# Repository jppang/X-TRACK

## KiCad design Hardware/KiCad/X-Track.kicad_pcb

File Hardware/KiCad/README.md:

使用KiCad來重新設計X-TRACK之原理圖及電路圖。

Utilizing KiCad to redesign X-TRACK's schematic and pcb layout.

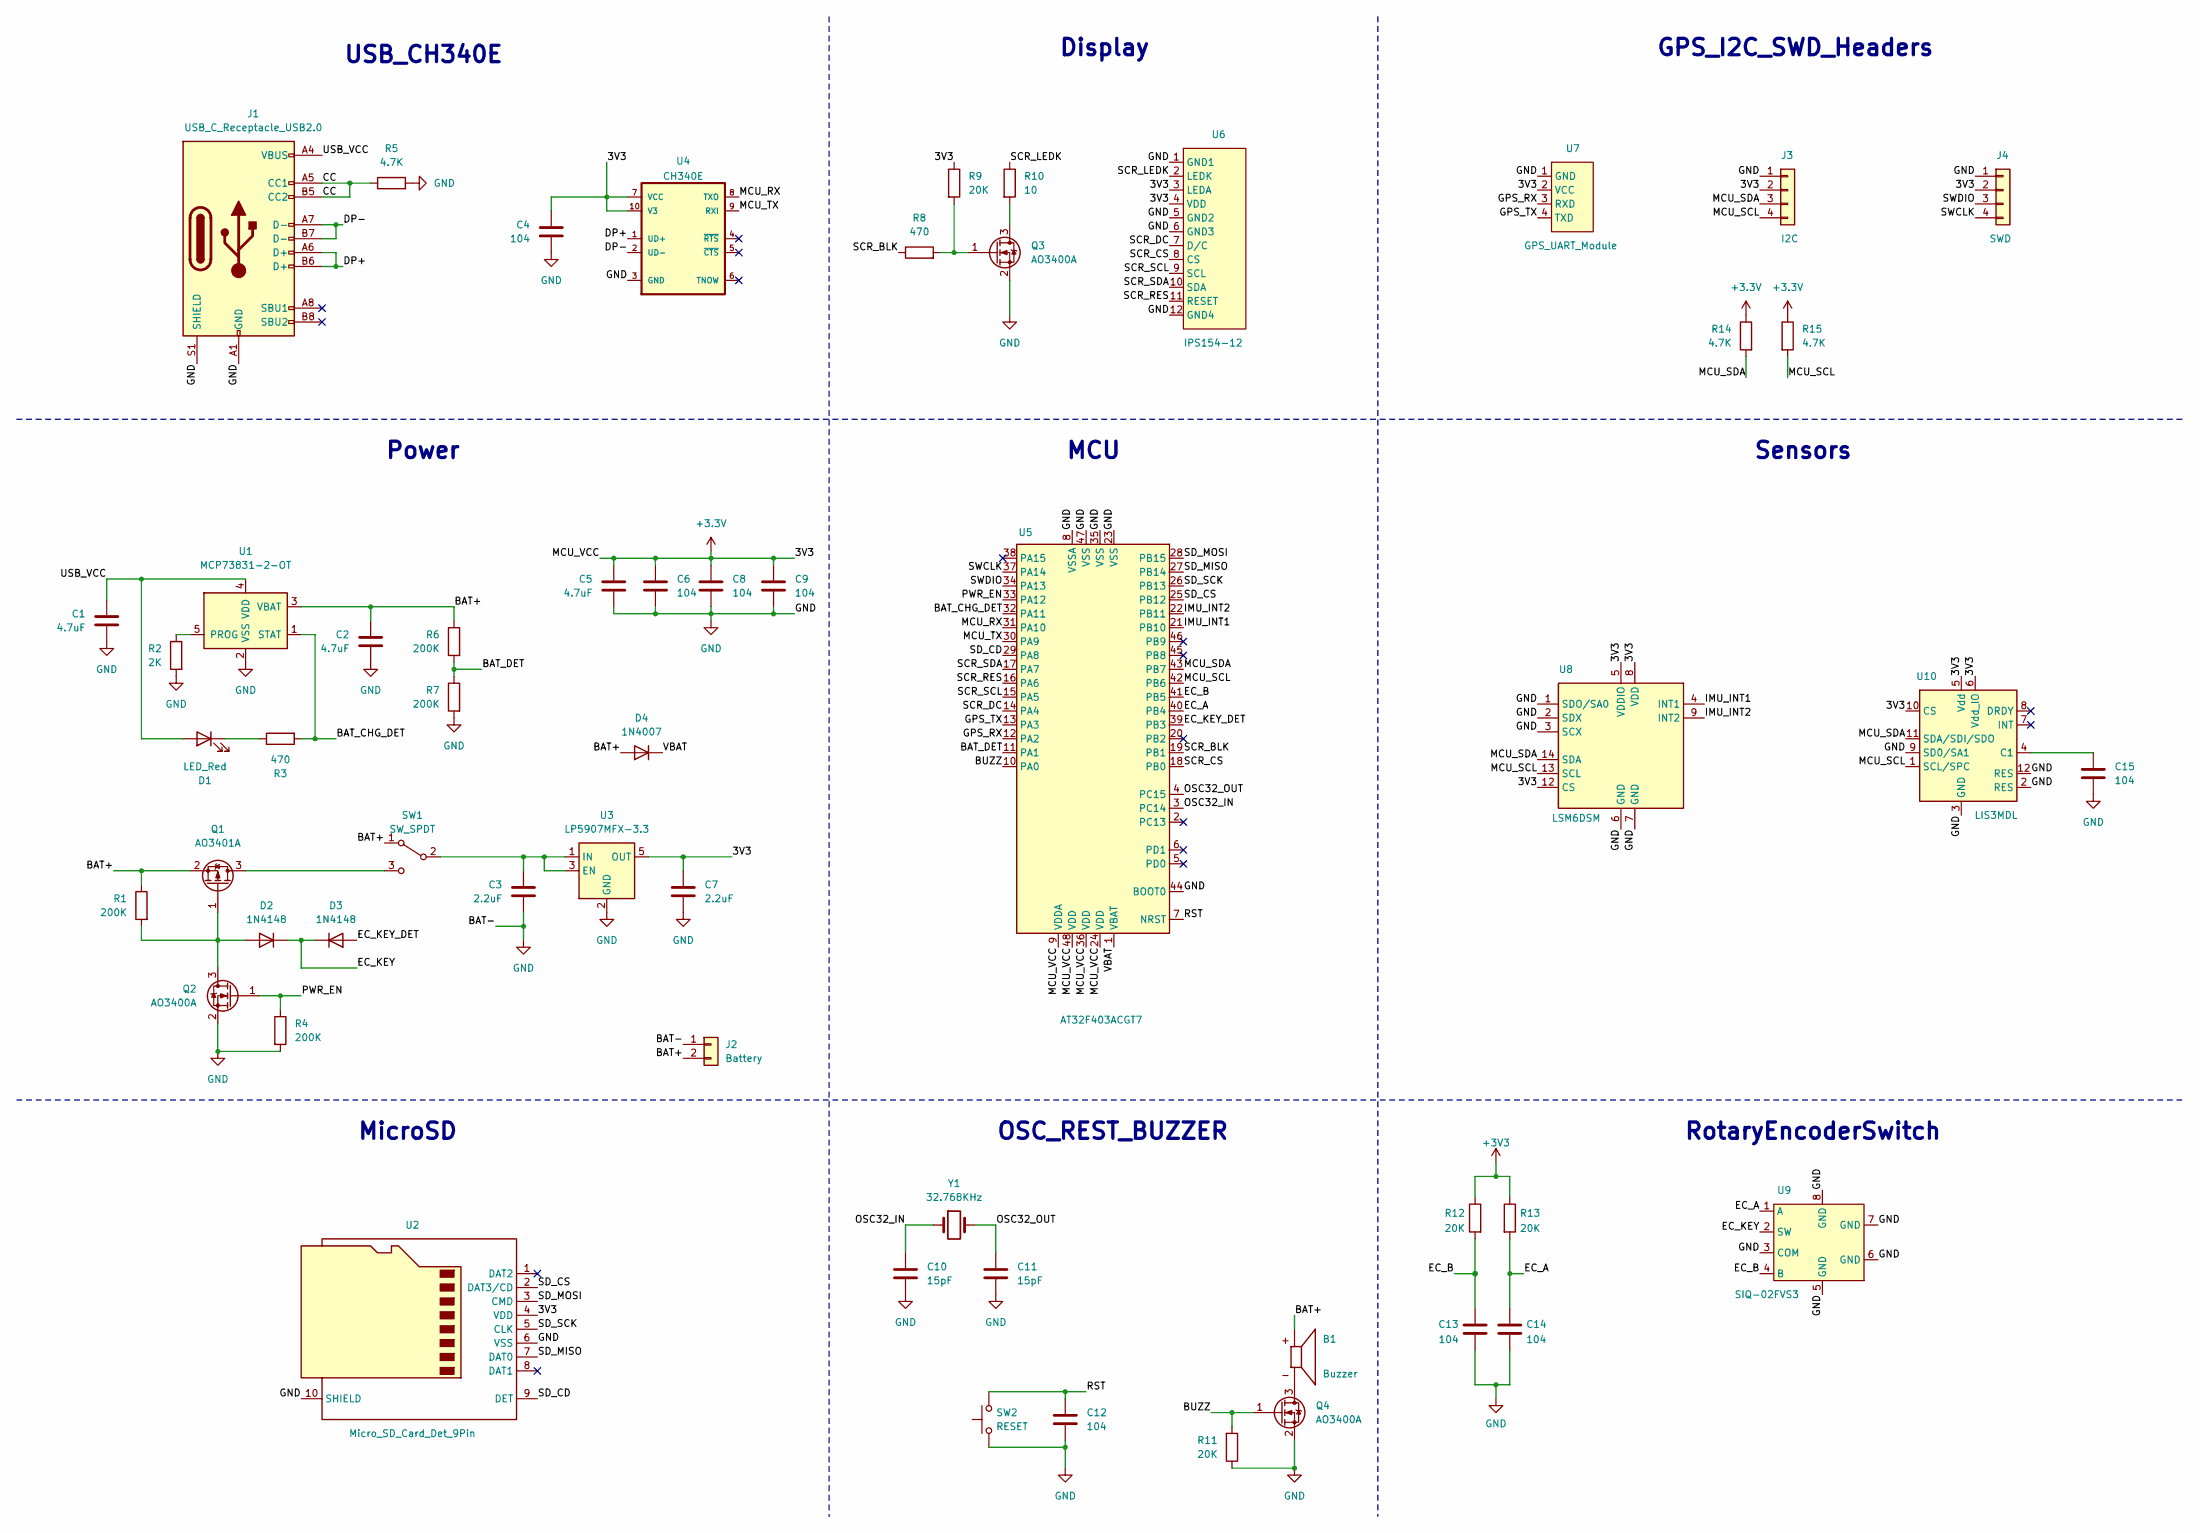
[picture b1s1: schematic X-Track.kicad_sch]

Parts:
B1: Buzzer; Buzzer_CMT-0502-75-SMT-TR; PARTREV 1.0
C1, C2, C5: 4.7uF; C_0805_2012Metric_Pad1.18x1.45mm_HandSolder
C3, C7: 2.2uF; C_0805_2012Metric_Pad1.18x1.45mm_HandSolder
C4, C6, C8, C9, C12, C13, C14, C15: 104; C_0805_2012Metric_Pad1.18x1.45mm_HandSolder
C10, C11: 15pF; C_0805_2012Metric_Pad1.18x1.45mm_HandSolder
D1: LED_Red; LED_0805_2012Metric_Pad1.15x1.40mm_HandSolder
D2, D3: 1N4148; D_0805_2012Metric_Pad1.15x1.40mm_HandSolder
D4: 1N4007; D_0805_2012Metric_Pad1.15x1.40mm_HandSolder
J1: USB_C_Receptacle_USB2.0; Taobao_USB_C_Receptacle_16Pin
J2: Battery; JST_PH_B2B-PH-K_1x02_P2.00mm_Vertical
J3: I2C; JST_PH_B4B-PH-K_1x04_P2.00mm_Vertical
J4: SWD; JST_PH_B4B-PH-K_1x04_P2.00mm_Vertical
Q1: AO3401A; SOT-23
Q2, Q3, Q4: AO3400A; SOT-23
R1, R4, R6, R7: 200K; R_0805_2012Metric_Pad1.20x1.40mm_HandSolder
R2: 2K; R_0805_2012Metric_Pad1.20x1.40mm_HandSolder
R3, R8: 470; R_0805_2012Metric_Pad1.20x1.40mm_HandSolder
R5, R14, R15: 4.7K; R_0805_2012Metric_Pad1.20x1.40mm_HandSolder
R9, R11, R12, R13: 20K; R_0805_2012Metric_Pad1.20x1.40mm_HandSolder
R10: 10; R_0805_2012Metric_Pad1.20x1.40mm_HandSolder
SW1: SW_SPDT; Taobao_SW_SPDT_MSK-12C01-07
SW2: RESET; SW_Push_SPST_NO_Alps_SKRK
U1: MCP73831-2-OT; SOT-23-5
U2: Micro_SD_Card_Det_9Pin; microSD_9Pins
U3: LP5907MFX-3.3; SOT-23-5
U4: CH340E; MSOP-10_3x3mm_P0.5mm
U5: AT32F403ACGT7; LQFP_LQFN_-48_7x7mm_P0.5mm
U6: IPS154-12; ZJY154T-PG04
U7: GPS_UART_Module; JST_PH_B4B-PH-K_1x04_P2.00mm_Vertical
U8: LSM6DSM; LGA-14L_2.5x3mm_P0.5mm_LSM6DSM
U9: SIQ-02FVS3; RotaryEncoder_Mitsumi_SIQ-02FVS3
U10: LIS3MDL; LGA-12_2x2mm_P0.5mm_LIS3MDL
Y1: 32.768KHz; Crystal_SMD_3215-2Pin_3.2x1.5mm

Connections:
/BAT+: B1.P, C2.2, D4.2 (A), J2.2, Q1.2 (S), R1.1, R6.1, SW1.1 (A), U1.3 (VBAT)
/BAT_CHG_DET: R3.2, U1.1 (STAT), U5.32 (PA11)
/BAT_DET: R6.2, R7.1, U5.11 (PA1)
/BUZZ: Q4.1 (G), R11.2, U5.10 (PA0)
/CC: J1.A5 (CC1), J1.B5 (CC2), R5.1
/DP+: J1.A6 (D+), J1.B6 (D+), U4.1 (UD+)
/DP-: J1.A7 (D-), J1.B7 (D-), U4.2 (UD-)
/EC_A: C14.1, R13.2, U5.40 (PB4), U9.1 (A)
/EC_B: C13.1, R12.2, U5.41 (PB5), U9.4 (B)
/EC_KEY: D2.1 (K), D3.1 (K), U9.2 (SW)
/EC_KEY_DET: D3.2 (A), U5.39 (PB3)
/GPS_RX: U5.12 (PA2), U7.3 (RXD)
/GPS_TX: U5.13 (PA3), U7.4 (TXD)
/IMU_INT1: U5.21 (PB10), U8.4 (INT1)
/IMU_INT2: U5.22 (PB11), U8.9 (INT2)
/MCU_RX: U4.8 (TXO), U5.31 (PA10)
/MCU_SCL: J3.4, R15.2, U5.42 (PB6), U8.13 (SCL), U10.1 (SCL/SPC)
/MCU_SDA: J3.3, R14.2, U5.43 (PB7), U8.14 (SDA), U10.11 (SDA/SDI/SDO)
/MCU_TX: U4.9 (RXI), U5.30 (PA9)
/OSC32_IN: C10.2, U5.3 (PC14), Y1.1
/OSC32_OUT: C11.1, U5.4 (PC15), Y1.2
/PWR_EN: Q2.1 (G), R4.1, U5.33 (PA12)
/RST: C12.1, SW2.2, U5.7 (NRST); also elsewhere on the board
/SCR_BLK: R8.1, U5.19 (PB1)
/SCR_CS: U5.18 (PB0), U6.8 (CS)
/SCR_DC: U5.14 (PA4), U6.7 (D/C)
/SCR_LEDK: R10.1, U6.2 (LEDK)
/SCR_RES: U5.16 (PA6), U6.11 (RESET)
/SCR_SCL: U5.15 (PA5), U6.9 (SCL)
/SCR_SDA: U5.17 (PA7), U6.10 (SDA)
/SD_CD: U2.9 (DET), U5.29 (PA8)
/SD_CS: U2.2 (DAT3/CD), U5.25 (PB12)
/SD_MISO: U2.7 (DAT0), U5.27 (PB14)
/SD_MOSI: U2.3 (CMD), U5.28 (PB15)
/SD_SCK: U2.5 (CLK), U5.26 (PB13)
/SWCLK: J4.4, U5.37 (PA14)
/SWDIO: J4.3, U5.34 (PA13)
/USB_VCC: C1.1, D1.2 (A), J1.A4 (VBUS), J1.A9 (VBUS), J1.B4 (VBUS), J1.B9 (VBUS), U1.4 (VDD)
/VBAT: D4.1 (K), U5.1 (VBAT)
GND: C1.2, C2.1, C3.2, C4.2, C5.2, C6.2, C7.2, C8.2, C9.2, C10.1, C11.2, C12.2, C13.2, C14.2, C15.2, J1.A1 (GND), J1.A12 (GND), J1.B1 (GND), J1.B12 (GND), J1.S1 (SHIELD), J2.1, J3.1, J4.1, Q2.2 (S), Q3.2 (S), Q4.2 (S), R2.2, R4.2, R5.2, R7.2, R11.1, SW2.1, U1.2 (VSS), U2.6 (VSS), U2.10 (SHIELD), U3.2 (GND), U4.3 (GND), U5.8 (VSSA), U5.23 (VSS), U5.35 (VSS), U5.44 (BOOT0), U5.47 (VSS), U6.1 (GND1), U6.5 (GND2), U6.6 (GND3), U6.12 (GND4), U7.1 (GND), U8.1 (SDO/SA0), U8.2 (SDX), U8.3 (SCX), U8.6 (GND), U8.7 (GND), U9.3 (COM), U9.5 (GND), U9.6 (GND), U9.7 (GND), U9.8 (GND), U10.2 (RES), U10.3 (GND), U10.9 (SD0/SA1), U10.12 (RES); also elsewhere on the board
unnamed: B1.N, Q4.3 (D)
unnamed: C3.1, SW1.2 (B), U3.1 (IN), U3.3 (EN)
unnamed: C15.1, U10.4 (C1)
unnamed: D1.1 (K), R3.1
unnamed: D2.2 (A), Q1.1 (G), Q2.3 (D), R1.2
unnamed: Q1.3 (D), SW1.3 (C)
unnamed: Q3.1 (G), R8.2, R9.2
unnamed: Q3.3 (D), R10.2
unnamed: R2.1, U1.5 (PROG)

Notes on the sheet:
RotaryEncoderSwitch
OSC_REST_BUZZER
GPS_I2C_SWD_Headers
MicroSD
USB_CH340E
Sensors
Power
Display
MCU

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
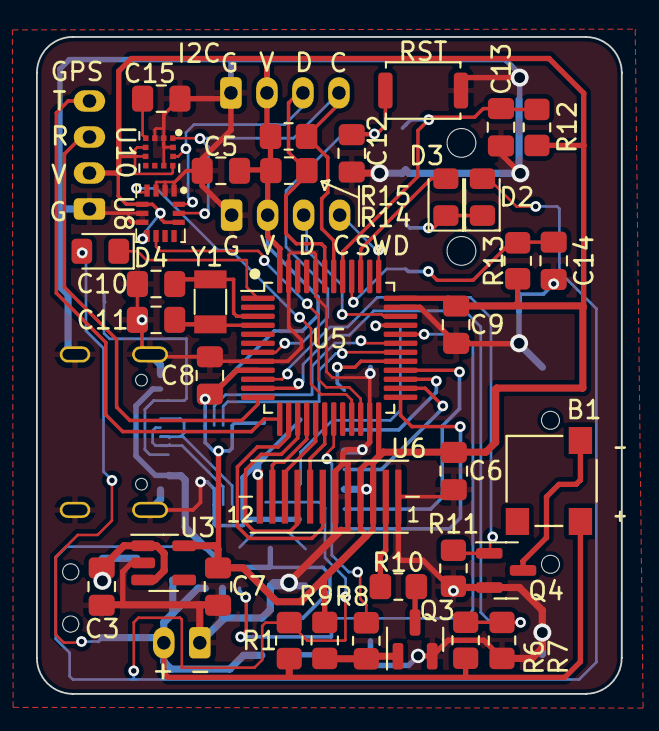
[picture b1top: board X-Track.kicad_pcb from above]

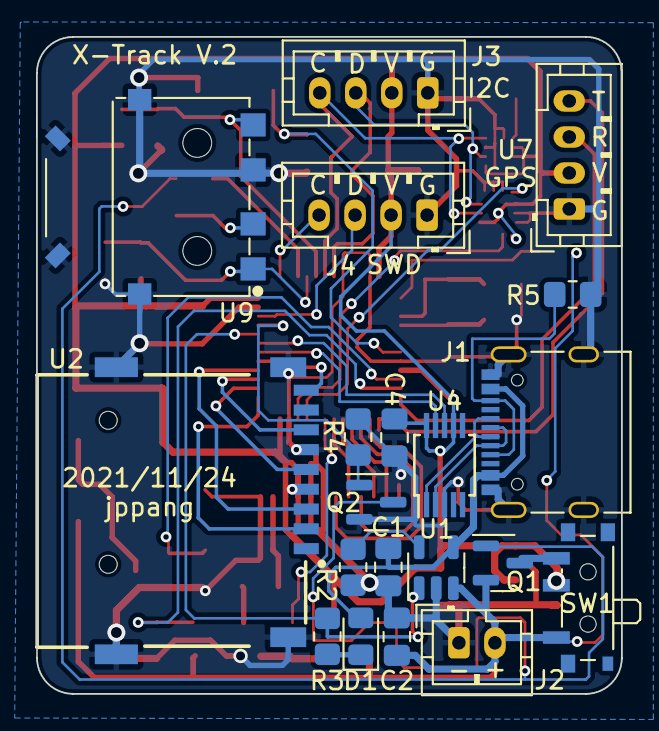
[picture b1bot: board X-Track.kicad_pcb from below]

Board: 2 copper layers, 32.5 x 36.5 mm, 56 parts (20 on the bottom side), 50 nets.

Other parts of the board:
RST: RESET; SW_Push_SPST_NO_Alps_SKRK

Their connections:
/RST: RST.2; also elsewhere on the board
GND: RST.1; also elsewhere on the board

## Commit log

2021-12-23 Create .gitkeep
    KiCad Implementation of X-TRACK.
2021-12-23 Add files via upload
    Add schematic and pcb files.
2021-12-23 Create .gitkeep
    Documents related to devices.
2021-12-23 Create .gitkeep
    Documents related to display.
2021-12-23 Add files via upload
    Documents related to display.
2021-12-23 Delete .gitkeep
    No need this file template.
2021-12-23 Create README.md
    X-TRACK by KiCad.
2021-12-23 Update README.md
    Add 3D images of pcb.
2022-02-01 使用TinkerCad設計的外殼
    前殼與背殼使用3D列印FDM的方式。
